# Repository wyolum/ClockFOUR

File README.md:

ClockFOUR
=========

ClockFOUR is a word clock that tells time with words.  It has a 14x13 matrix of letters that, when illuminated, tells time to the minute.  e.g. SEVENTEEN MINUTES PAST FOUR  The clock is 28 x 28 x ~2.6 cm.  The main PCB is approximately 24 x 22 cm and has 182 RGB WS2812B pixels on the front.  The back of the PCB contains an Arduino compatible 328P microprocessor and a DS3231 real time clock chip with 2032 battery backup.  Power is provided by a quality international multi-voltage 5V 3A power supply with barrel connector.

The user interface consists of two touch sensitive buttons wired to top two metal screw posts. Modes and settings are actuated by short taps and long presses.

Development team:
David Pincus (Project leader, software, hardware & design)
Josef Schneider (Software)
Anool Mahidharia (Hardware)

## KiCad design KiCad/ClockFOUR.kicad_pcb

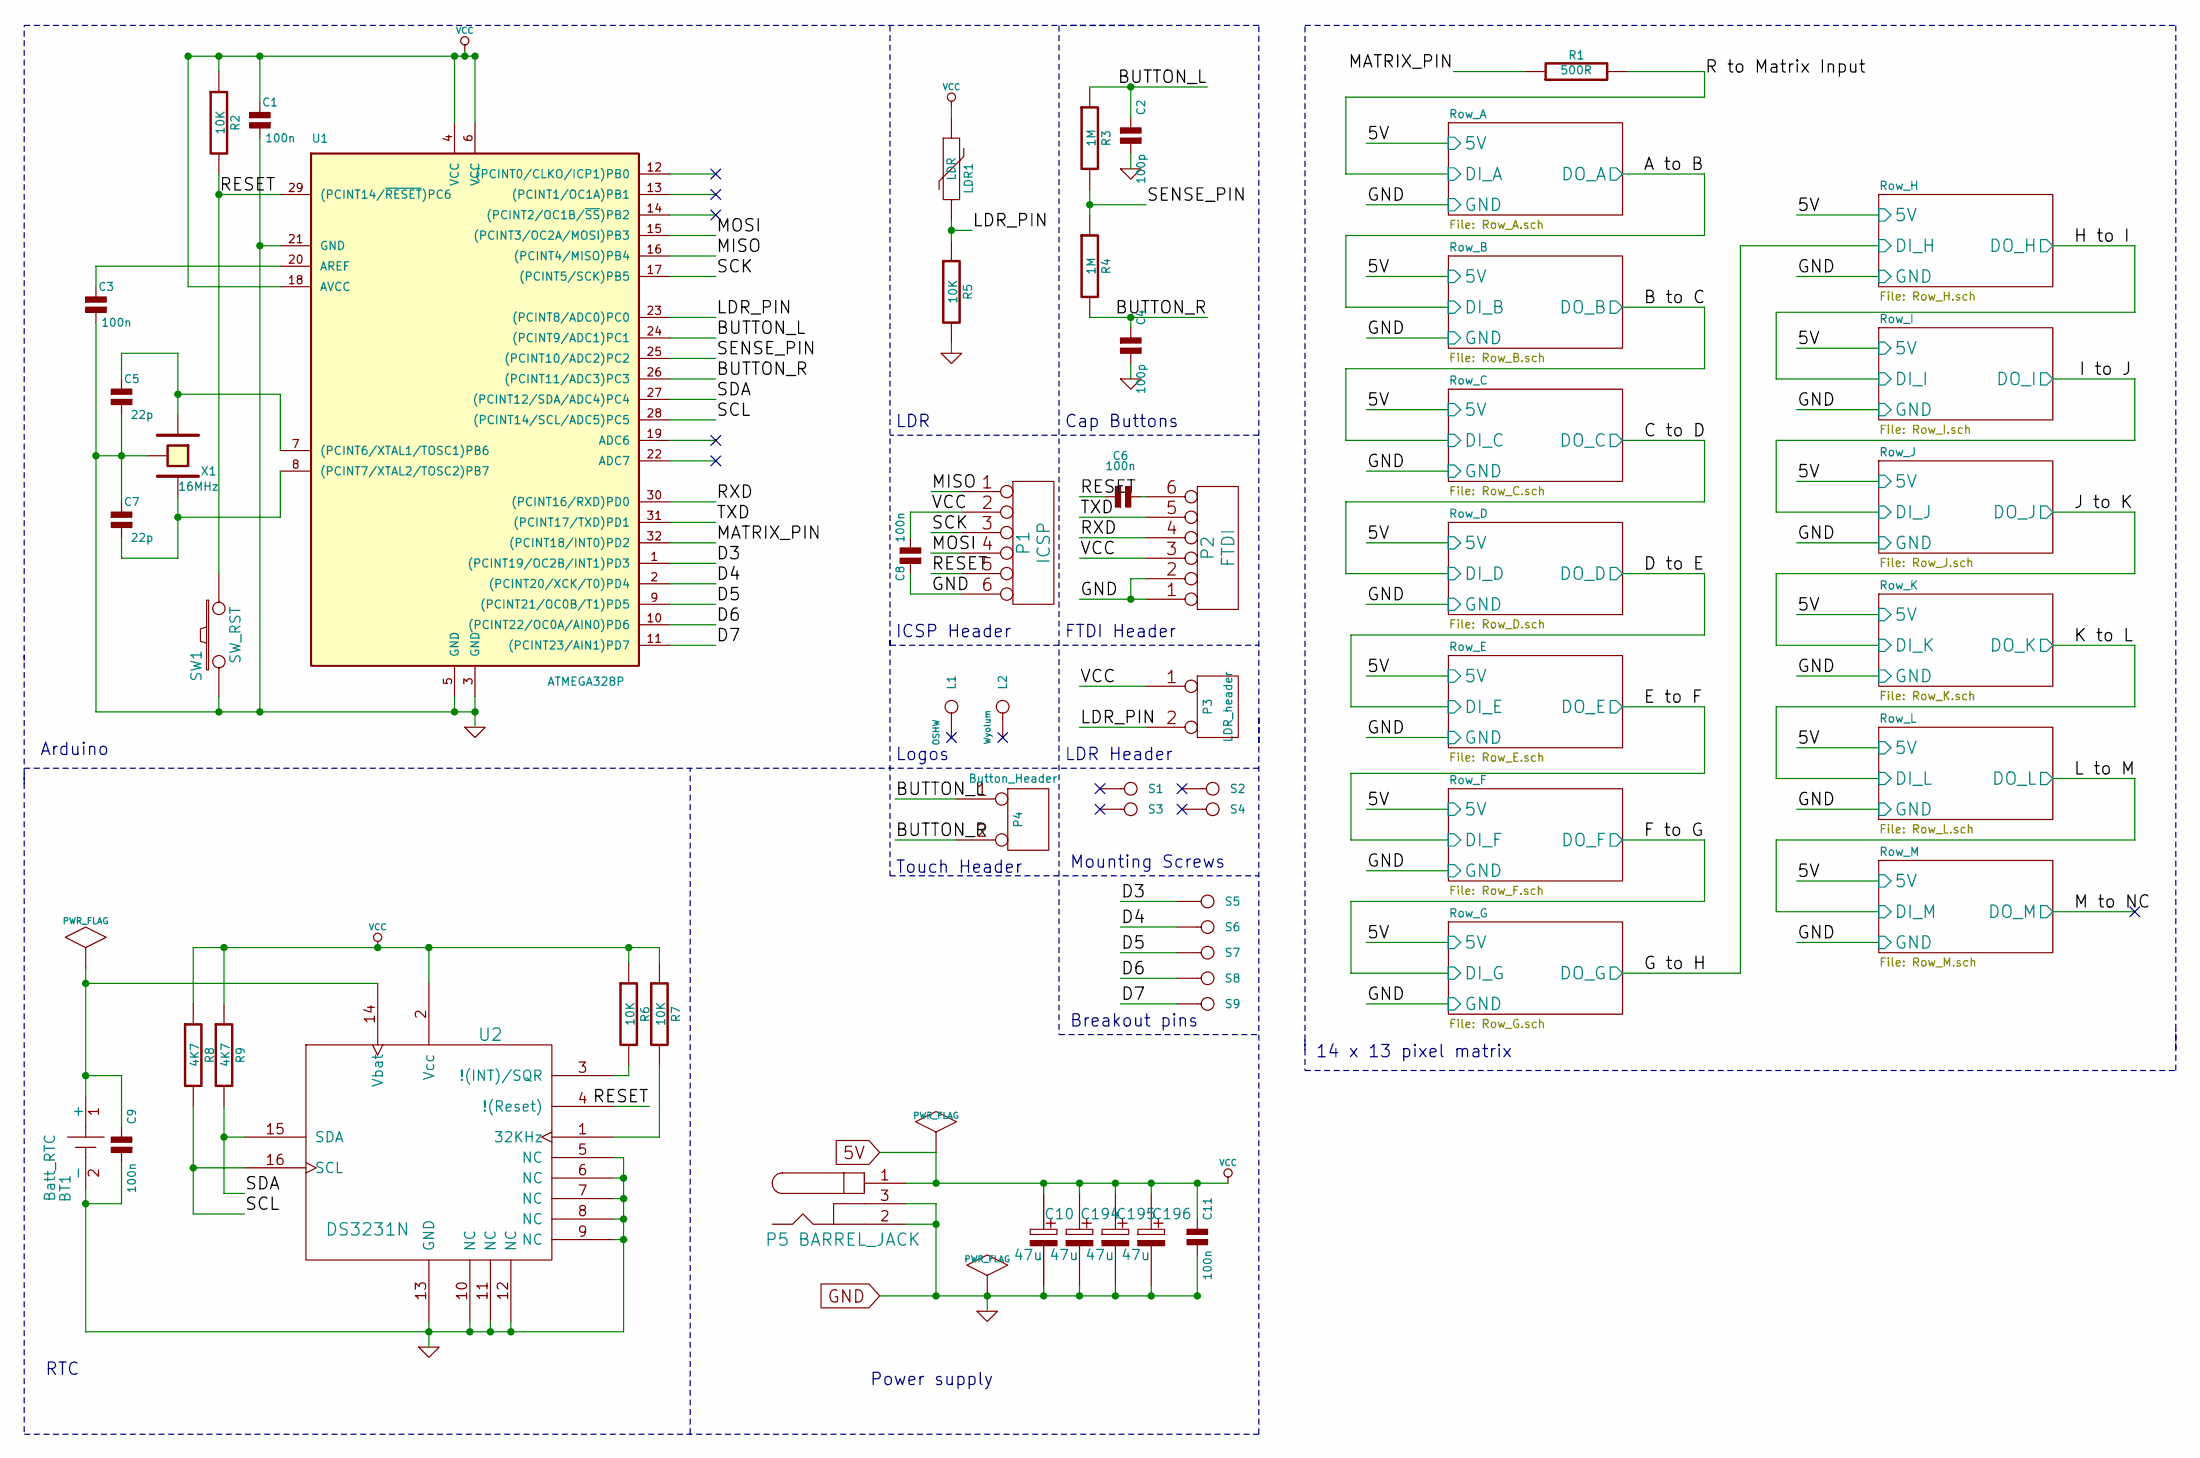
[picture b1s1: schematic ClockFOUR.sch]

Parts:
BT1: Batt_RTC; CR2032; Digikey BU2032SM-HD-GCT-ND
C1, C3, C6, C8, C9, C11: 100n; c_0805
C2, C4: 100p; c_0805
C5, C7: 22p; c_0805
C10, C194, C195, C196: 47u; c_2917
L1: OSHW; Logo_silk_OSHW_6x6mm
L2: Wyolum; Logo-WL3
LDR1: LDR; r_0805
P1: ICSP; ISP
P2: FTDI; Header_FTDI
P3: LDR_header; SIL-2
P4: Button_Header; SIL-2
P5: BARREL_JACK; JACK_PJ-047a
R1: 500R; r_0805
R2, R5, R6, R7: 10K; r_0805
R3, R4: 1M; r_0805
R8, R9: 4K7; r_0805
S1, S2, S3, S4: CONN_1; Screw_3mm
S5, S6, S7, S8, S9: CONN_1; BreakOutPad
SW1: SW_RST; SW_PB_V_H
U1: ATMEGA328P; TQFP32
U2: DS3231N; DS3231
X1: 16MHz

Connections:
5V: C1.1, C8.2, C10.1 (+), C11.1, C194.1 (+), C195.1 (+), C196.1 (+), LDR1.1, P1.2, P2.3, P3.1, P5.1, R2.1, R6.1, R7.1, R8.1, R9.1, U1.4 (VCC), U1.6 (VCC), U1.18 (AVCC), U2.2 (Vcc); also elsewhere on the board
/BUTTON_L: C2.1, P4.1, R3.1, U1.24 ((PCINT9/ADC1)PC1)
/BUTTON_R: C4.1, P4.2 (PM), R4.2, U1.26 ((PCINT11/ADC3)PC3)
/D3: S5.1, U1.1 ((PCINT19/OC2B/INT1)PD3)
/D4: S6.1, U1.2 ((PCINT20/XCK/T0)PD4)
/D5: S7.1, U1.9 ((PCINT21/OC0B/T1)PD5)
/D6: S8.1, U1.10 ((PCINT22/OC0A/AIN0)PD6)
/D7: S9.1, U1.11 ((PCINT23/AIN1)PD7)
/LDR_PIN: LDR1.2, P3.2 (PM), R5.1, U1.23 ((PCINT8/ADC0)PC0)
/MATRIX_PIN: R1.1, U1.32 ((PCINT18/INT0)PD2)
/MISO: P1.1, U1.16 ((PCINT4/MISO)PB4)
/MOSI: P1.4, U1.15 ((PCINT3/OC2A/MOSI)PB3)
/RESET: C6.1, P1.5, R2.2, SW1.1, U1.29 ((PCINT14/~RESET~)PC6), U2.4 (!(Reset))
/RXD: P2.4, U1.30 ((PCINT16/RXD)PD0)
/Row_A/DI_A: R1.2; also elsewhere on the board
/SCK: P1.3, U1.17 ((PCINT5/SCK)PB5)
/SCL: R8.2, U1.28 ((PCINT14/SCL/ADC5)PC5), U2.16 (SCL)
/SDA: R9.2, U1.27 ((PCINT12/SDA/ADC4)PC4), U2.15 (SDA)
/SENSE_PIN: R3.2, R4.1, U1.25 ((PCINT10/ADC2)PC2)
/TXD: P2.5, U1.31 ((PCINT17/TXD)PD1)
GND: BT1.2 (-), C1.2, C2.2, C3.2, C4.2, C5.2, C7.1, C8.1, C9.2, C10.2 (-), C11.2, C194.2 (-), C195.2 (-), C196.2 (-), P1.6, P2.1, P2.2, P5.2, P5.3, R5.2, SW1.2, U1.3 (GND), U1.5 (GND), U1.21 (GND), U2.5 (NC), U2.6 (NC), U2.7 (NC), U2.8 (NC), U2.9 (NC), U2.10 (NC), U2.11 (NC), U2.12 (NC), U2.13 (GND), X1.3; also elsewhere on the board
unnamed: BT1.1 (+), C9.1, U2.14 (Vbat)
unnamed: C3.1, U1.20 (AREF)
unnamed: C5.1, U1.7 ((PCINT6/XTAL1/TOSC1)PB6), X1.1
unnamed: C6.2, P2.6
unnamed: C7.2, U1.8 ((PCINT7/XTAL2/TOSC2)PB7), X1.2
unnamed: R6.2, U2.3 (!(INT)/SQR)
unnamed: R7.2, U2.1 (32KHz)

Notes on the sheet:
14 x 13 pixel matrix
RTC
Power supply
LDR
Cap Buttons
Arduino
ICSP Header
FTDI Header
LDR Header
Logos
Mounting Screws
Touch Header
Breakout pins

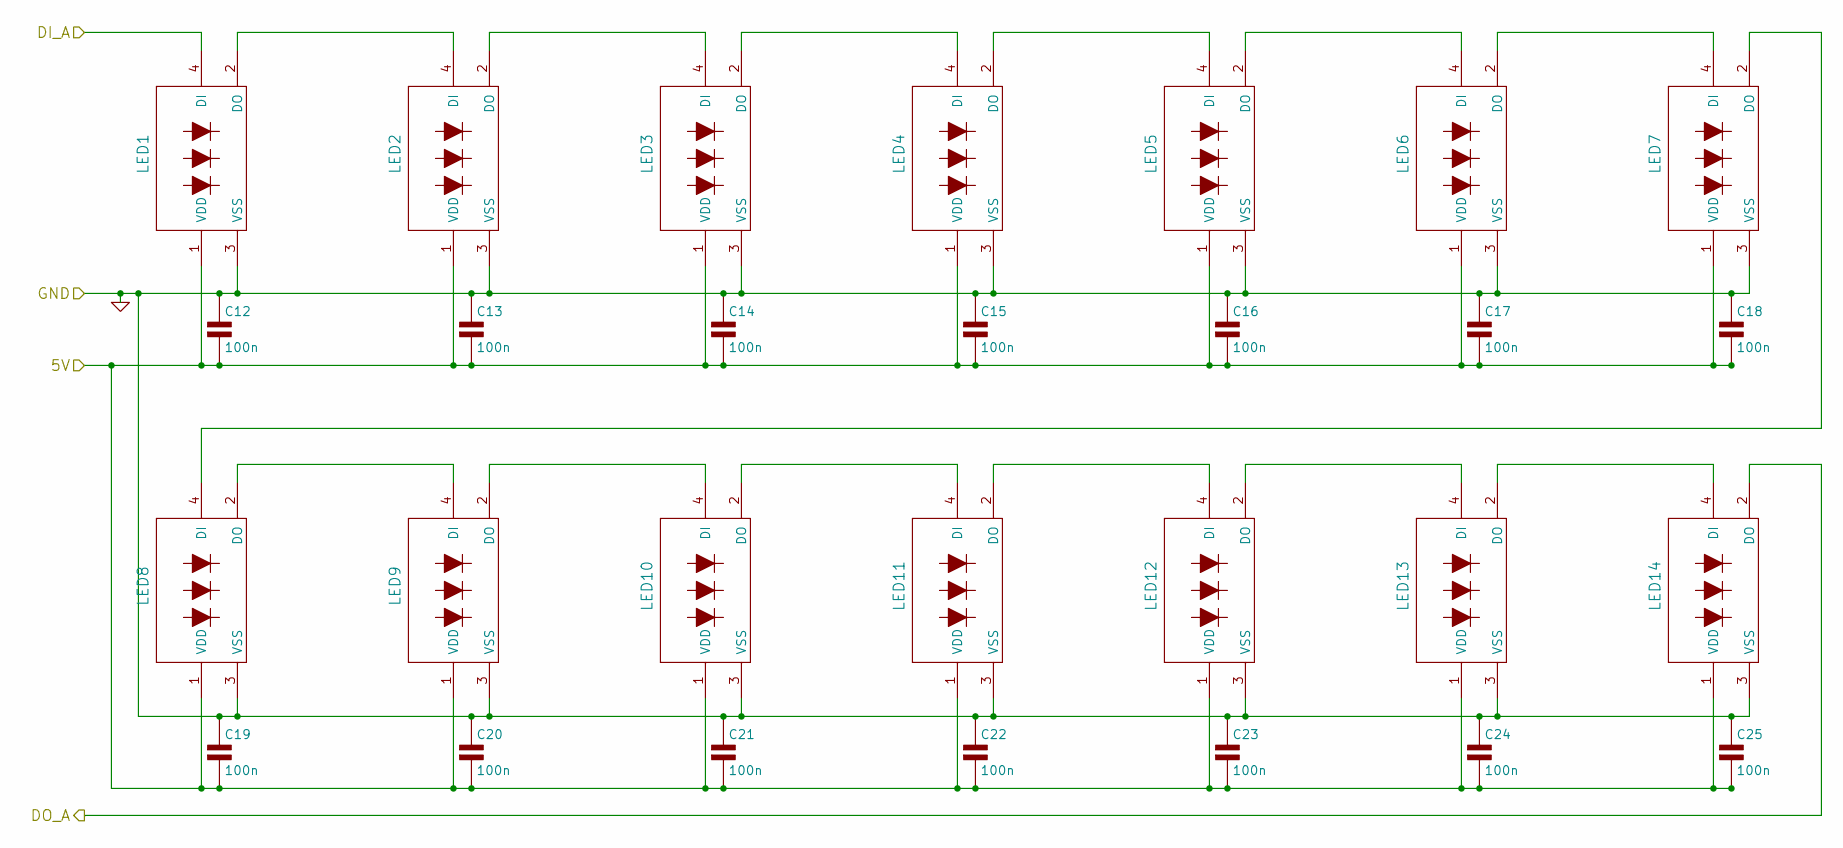
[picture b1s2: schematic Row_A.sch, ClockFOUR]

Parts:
C12, C13, C14, C15, C16, C17, C18, C19, C20, C21, C22, C23, C24, C25: 100n; c_0805
LED1, LED2, LED3, LED4, LED5, LED6, LED7, LED8, LED9, LED10, LED11, LED12, LED13, LED14: WS2812B

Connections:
5V: C12.2, C13.2, C14.2, C15.2, C16.2, C17.2, C18.2, C19.2, C20.2, C21.2, C22.2, C23.2, C24.2, C25.2, LED1.1 (VDD), LED2.1 (VDD), LED3.1 (VDD), LED4.1 (VDD), LED5.1 (VDD), LED6.1 (VDD), LED7.1 (VDD), LED8.1 (VDD), LED9.1 (VDD), LED10.1 (VDD), LED11.1 (VDD), LED12.1 (VDD), LED13.1 (VDD), LED14.1 (VDD); also elsewhere on the board
/Row_A/DI_A: LED1.4 (DI); also elsewhere on the board
/Row_B/DI_B: LED14.2 (DO); also elsewhere on the board
GND: C12.1, C13.1, C14.1, C15.1, C16.1, C17.1, C18.1, C19.1, C20.1, C21.1, C22.1, C23.1, C24.1, C25.1, LED1.3 (VSS), LED2.3 (VSS), LED3.3 (VSS), LED4.3 (VSS), LED5.3 (VSS), LED6.3 (VSS), LED7.3 (VSS), LED8.3 (VSS), LED9.3 (VSS), LED10.3 (VSS), LED11.3 (VSS), LED12.3 (VSS), LED13.3 (VSS), LED14.3 (VSS); also elsewhere on the board
unnamed: LED1.2 (DO), LED2.4 (DI)
unnamed: LED2.2 (DO), LED3.4 (DI)
unnamed: LED3.2 (DO), LED4.4 (DI)
unnamed: LED4.2 (DO), LED5.4 (DI)
unnamed: LED5.2 (DO), LED6.4 (DI)
unnamed: LED6.2 (DO), LED7.4 (DI)
unnamed: LED7.2 (DO), LED8.4 (DI)
unnamed: LED8.2 (DO), LED9.4 (DI)
unnamed: LED10.2 (DO), LED11.4 (DI)
unnamed: LED9.2 (DO), LED10.4 (DI)
unnamed: LED11.2 (DO), LED12.4 (DI)
unnamed: LED12.2 (DO), LED13.4 (DI)
unnamed: LED13.2 (DO), LED14.4 (DI)

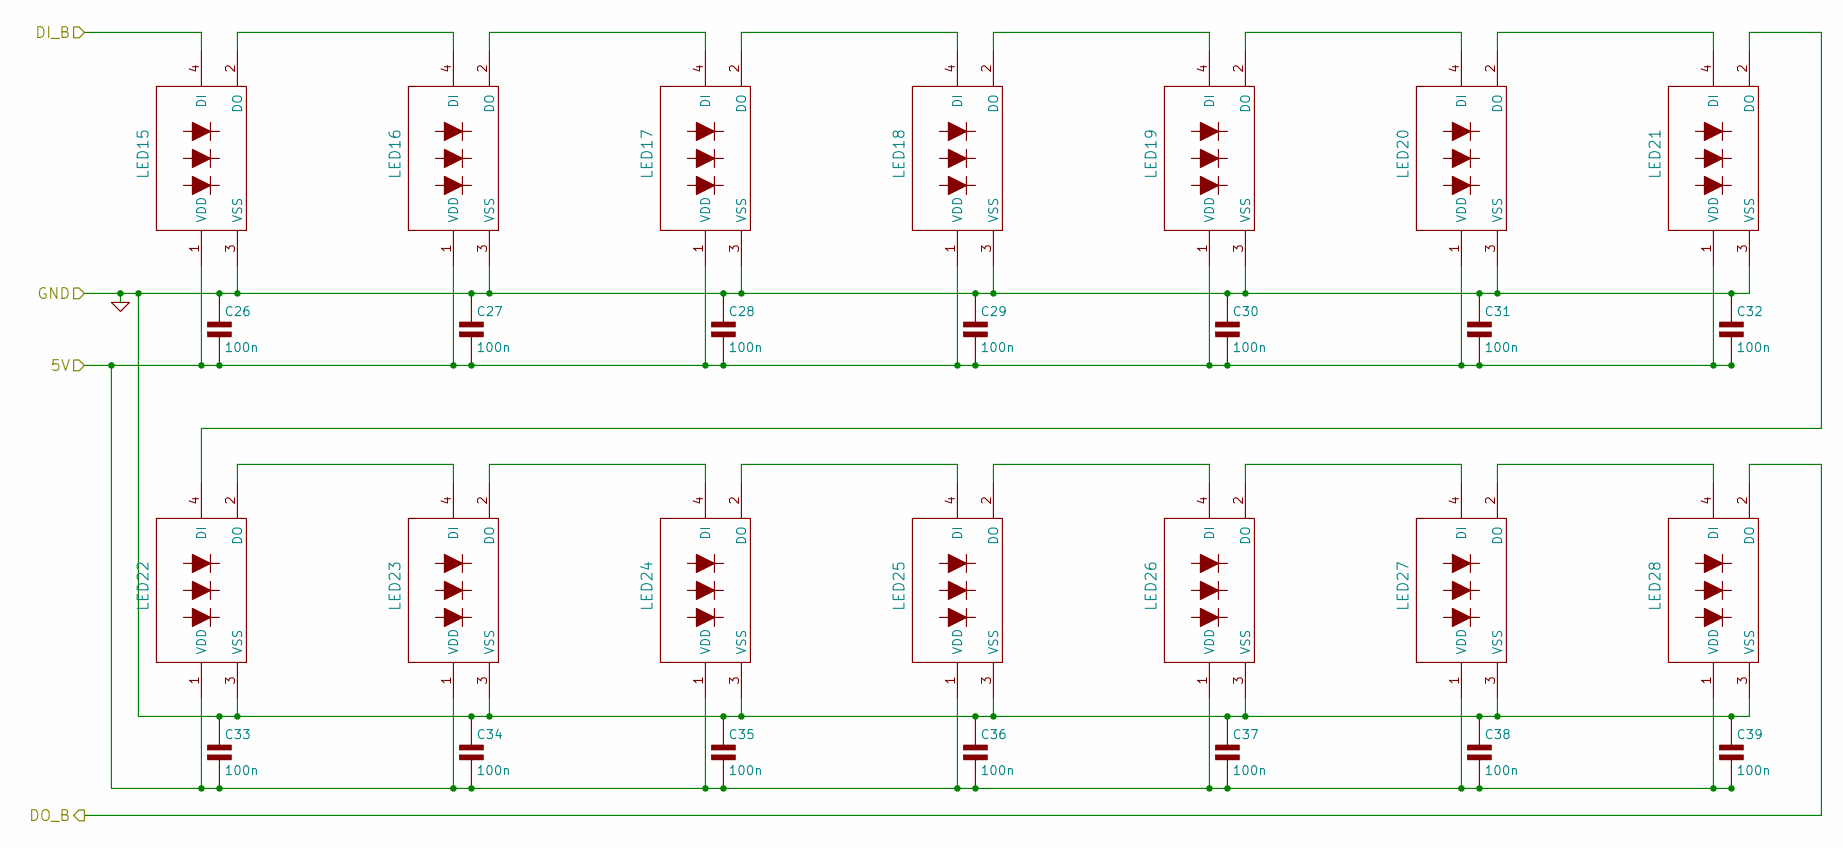
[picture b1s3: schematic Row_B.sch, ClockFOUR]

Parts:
C26, C27, C28, C29, C30, C31, C32, C33, C34, C35, C36, C37, C38, C39: 100n; c_0805
LED15, LED16, LED17, LED18, LED19, LED20, LED21, LED22, LED23, LED24, LED25, LED26, LED27, LED28: WS2812B

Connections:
5V: C26.2, C27.2, C28.2, C29.2, C30.2, C31.2, C32.2, C33.2, C34.2, C35.2, C36.2, C37.2, C38.2, C39.2, LED15.1 (VDD), LED16.1 (VDD), LED17.1 (VDD), LED18.1 (VDD), LED19.1 (VDD), LED20.1 (VDD), LED21.1 (VDD), LED22.1 (VDD), LED23.1 (VDD), LED24.1 (VDD), LED25.1 (VDD), LED26.1 (VDD), LED27.1 (VDD), LED28.1 (VDD); also elsewhere on the board
/Row_B/DI_B: LED15.4 (DI); also elsewhere on the board
/Row_C/DI_C: LED28.2 (DO); also elsewhere on the board
GND: C26.1, C27.1, C28.1, C29.1, C30.1, C31.1, C32.1, C33.1, C34.1, C35.1, C36.1, C37.1, C38.1, C39.1, LED15.3 (VSS), LED16.3 (VSS), LED17.3 (VSS), LED18.3 (VSS), LED19.3 (VSS), LED20.3 (VSS), LED21.3 (VSS), LED22.3 (VSS), LED23.3 (VSS), LED24.3 (VSS), LED25.3 (VSS), LED26.3 (VSS), LED27.3 (VSS), LED28.3 (VSS); also elsewhere on the board
unnamed: LED15.2 (DO), LED16.4 (DI)
unnamed: LED16.2 (DO), LED17.4 (DI)
unnamed: LED17.2 (DO), LED18.4 (DI)
unnamed: LED18.2 (DO), LED19.4 (DI)
unnamed: LED19.2 (DO), LED20.4 (DI)
unnamed: LED20.2 (DO), LED21.4 (DI)
unnamed: LED21.2 (DO), LED22.4 (DI)
unnamed: LED22.2 (DO), LED23.4 (DI)
unnamed: LED23.2 (DO), LED24.4 (DI)
unnamed: LED24.2 (DO), LED25.4 (DI)
unnamed: LED25.2 (DO), LED26.4 (DI)
unnamed: LED26.2 (DO), LED27.4 (DI)
unnamed: LED27.2 (DO), LED28.4 (DI)

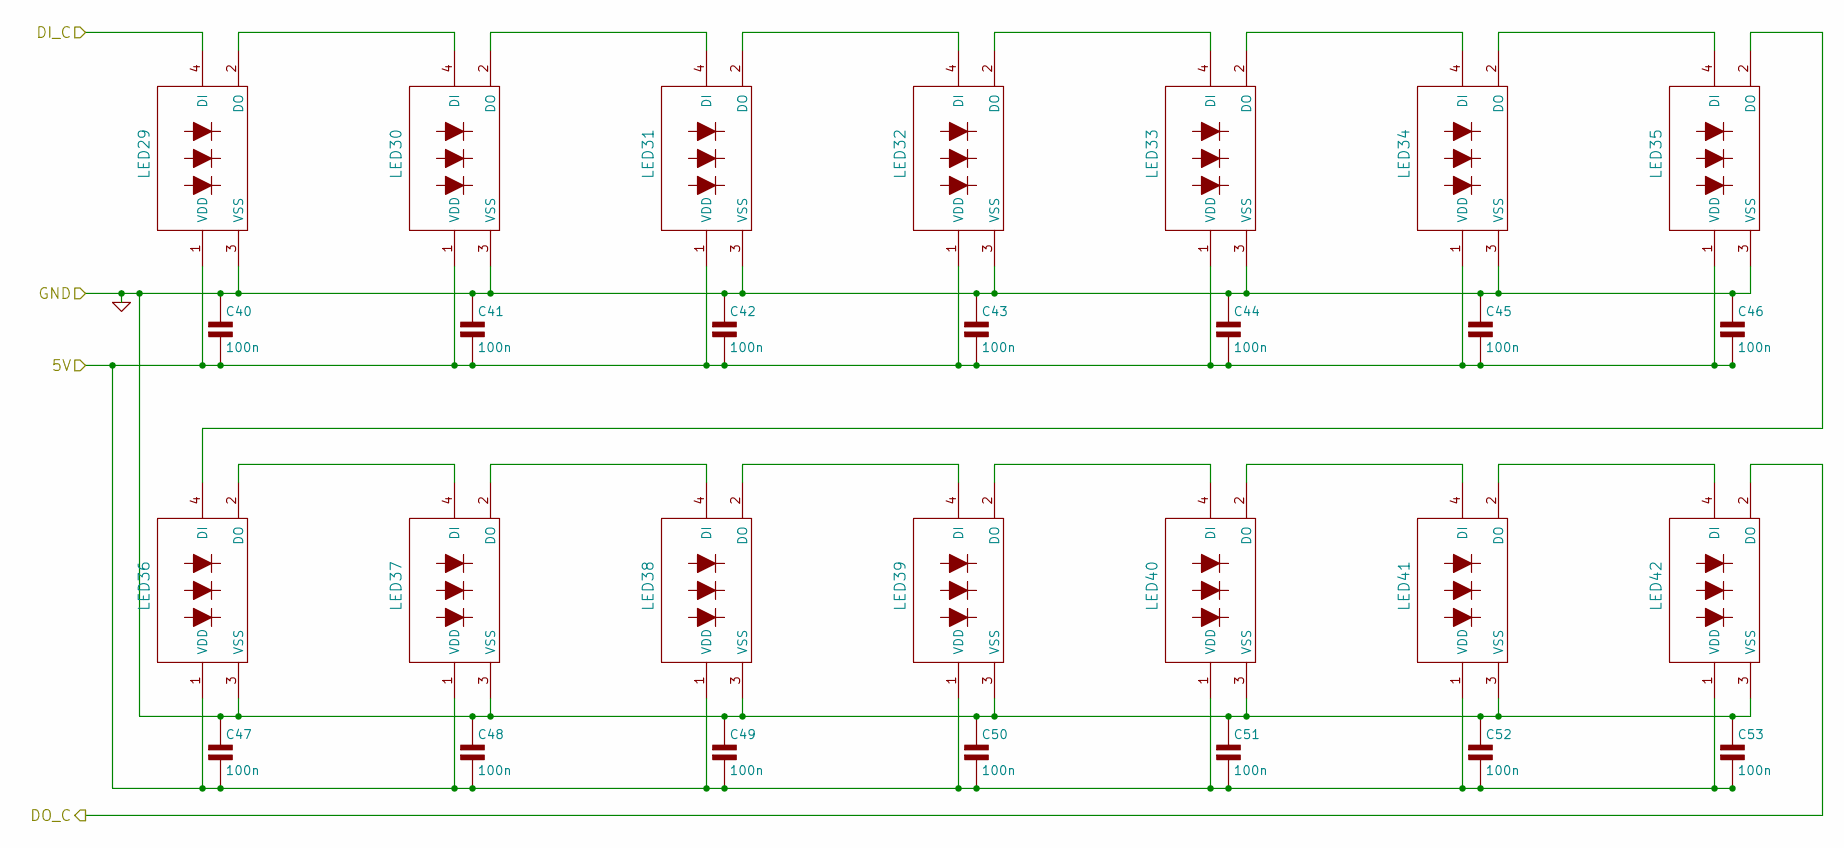
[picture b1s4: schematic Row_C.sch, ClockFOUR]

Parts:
C40, C41, C42, C43, C44, C45, C46, C47, C48, C49, C50, C51, C52, C53: 100n; c_0805
LED29, LED30, LED31, LED32, LED33, LED34, LED35, LED36, LED37, LED38, LED39, LED40, LED41, LED42: WS2812B; RGB_WS2811B

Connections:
5V: C40.2, C41.2, C42.2, C43.2, C44.2, C45.2, C46.2, C47.2, C48.2, C49.2, C50.2, C51.2, C52.2, C53.2, LED29.1 (VDD), LED30.1 (VDD), LED31.1 (VDD), LED32.1 (VDD), LED33.1 (VDD), LED34.1 (VDD), LED35.1 (VDD), LED36.1 (VDD), LED37.1 (VDD), LED38.1 (VDD), LED39.1 (VDD), LED40.1 (VDD), LED41.1 (VDD), LED42.1 (VDD); also elsewhere on the board
/Row_C/DI_C: LED29.4 (DI); also elsewhere on the board
/Row_D/DI_D: LED42.2 (DO); also elsewhere on the board
GND: C40.1, C41.1, C42.1, C43.1, C44.1, C45.1, C46.1, C47.1, C48.1, C49.1, C50.1, C51.1, C52.1, C53.1, LED29.3 (VSS), LED30.3 (VSS), LED31.3 (VSS), LED32.3 (VSS), LED33.3 (VSS), LED34.3 (VSS), LED35.3 (VSS), LED36.3 (VSS), LED37.3 (VSS), LED38.3 (VSS), LED39.3 (VSS), LED40.3 (VSS), LED41.3 (VSS), LED42.3 (VSS); also elsewhere on the board
unnamed: LED29.2 (DO), LED30.4 (DI)
unnamed: LED30.2 (DO), LED31.4 (DI)
unnamed: LED31.2 (DO), LED32.4 (DI)
unnamed: LED32.2 (DO), LED33.4 (DI)
unnamed: LED33.2 (DO), LED34.4 (DI)
unnamed: LED34.2 (DO), LED35.4 (DI)
unnamed: LED35.2 (DO), LED36.4 (DI)
unnamed: LED36.2 (DO), LED37.4 (DI)
unnamed: LED37.2 (DO), LED38.4 (DI)
unnamed: LED38.2 (DO), LED39.4 (DI)
unnamed: LED39.2 (DO), LED40.4 (DI)
unnamed: LED40.2 (DO), LED41.4 (DI)
unnamed: LED41.2 (DO), LED42.4 (DI)

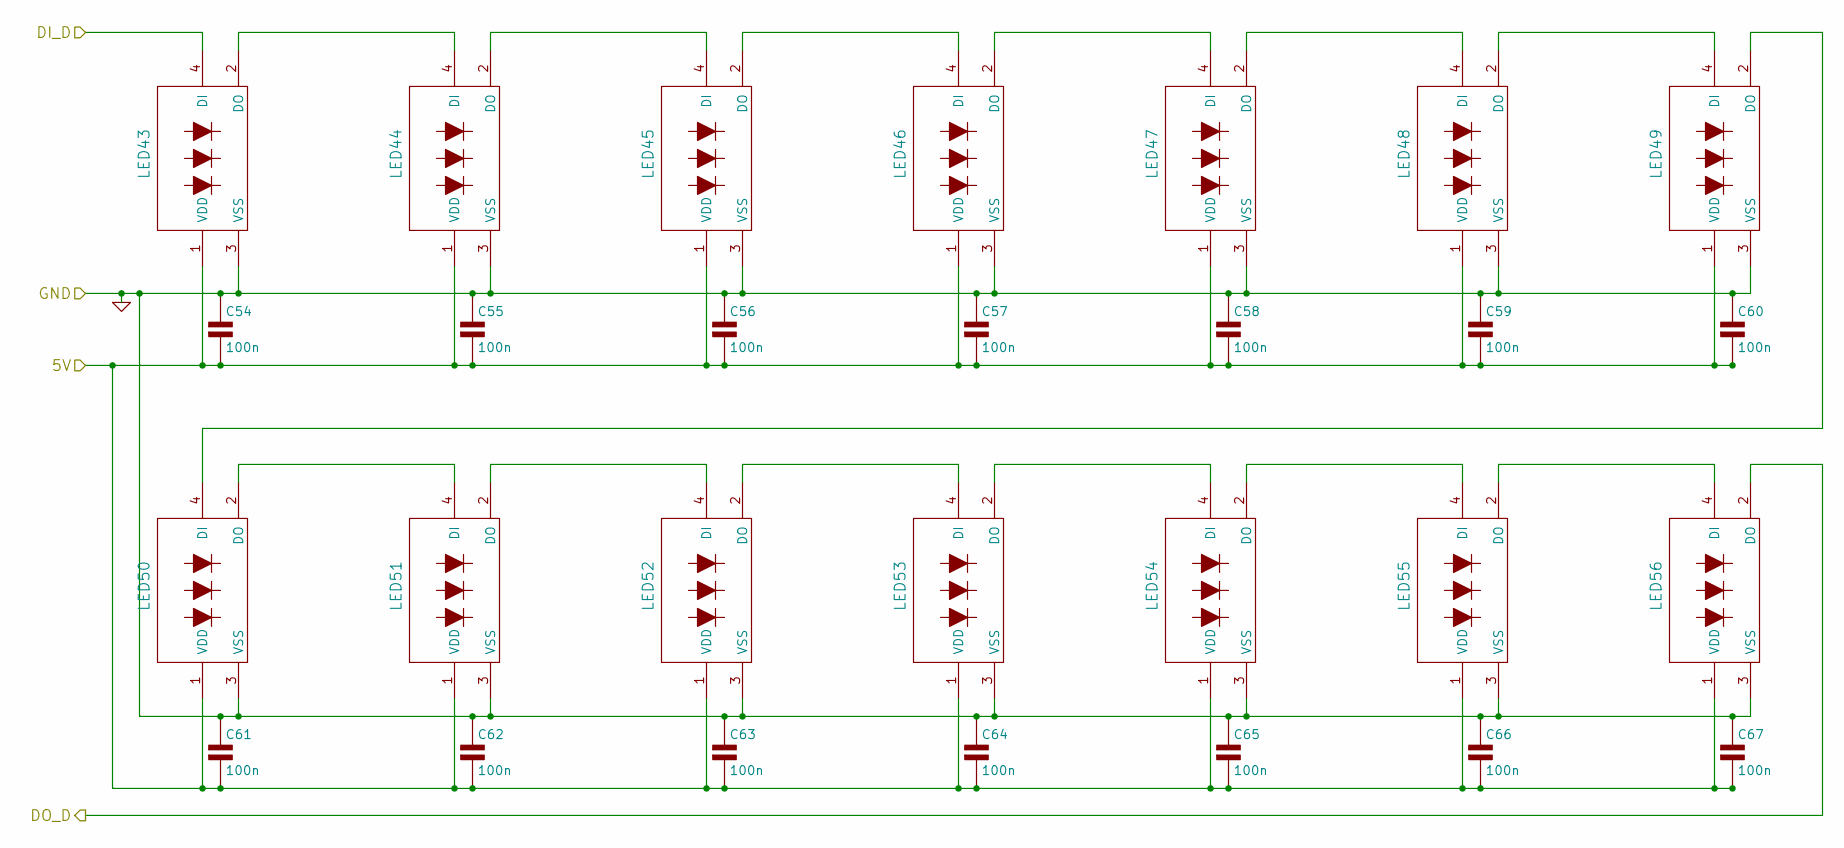
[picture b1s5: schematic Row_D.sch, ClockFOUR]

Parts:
C54, C55, C56, C57, C58, C59, C60, C61, C62, C63, C64, C65, C66, C67: 100n; c_0805
LED43, LED44, LED45, LED46, LED47, LED48, LED49, LED50, LED51, LED52, LED53, LED54, LED55, LED56: WS2812B; RGB_WS2811B

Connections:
5V: C54.2, C55.2, C56.2, C57.2, C58.2, C59.2, C60.2, C61.2, C62.2, C63.2, C64.2, C65.2, C66.2, C67.2, LED43.1 (VDD), LED44.1 (VDD), LED45.1 (VDD), LED46.1 (VDD), LED47.1 (VDD), LED48.1 (VDD), LED49.1 (VDD), LED50.1 (VDD), LED51.1 (VDD), LED52.1 (VDD), LED53.1 (VDD), LED54.1 (VDD), LED55.1 (VDD), LED56.1 (VDD); also elsewhere on the board
/Row_D/DI_D: LED43.4 (DI); also elsewhere on the board
/Row_E/DI_E: LED56.2 (DO); also elsewhere on the board
GND: C54.1, C55.1, C56.1, C57.1, C58.1, C59.1, C60.1, C61.1, C62.1, C63.1, C64.1, C65.1, C66.1, C67.1, LED43.3 (VSS), LED44.3 (VSS), LED45.3 (VSS), LED46.3 (VSS), LED47.3 (VSS), LED48.3 (VSS), LED49.3 (VSS), LED50.3 (VSS), LED51.3 (VSS), LED52.3 (VSS), LED53.3 (VSS), LED54.3 (VSS), LED55.3 (VSS), LED56.3 (VSS); also elsewhere on the board
unnamed: LED43.2 (DO), LED44.4 (DI)
unnamed: LED44.2 (DO), LED45.4 (DI)
unnamed: LED45.2 (DO), LED46.4 (DI)
unnamed: LED46.2 (DO), LED47.4 (DI)
unnamed: LED47.2 (DO), LED48.4 (DI)
unnamed: LED48.2 (DO), LED49.4 (DI)
unnamed: LED49.2 (DO), LED50.4 (DI)
unnamed: LED50.2 (DO), LED51.4 (DI)
unnamed: LED51.2 (DO), LED52.4 (DI)
unnamed: LED52.2 (DO), LED53.4 (DI)
unnamed: LED53.2 (DO), LED54.4 (DI)
unnamed: LED54.2 (DO), LED55.4 (DI)
unnamed: LED55.2 (DO), LED56.4 (DI)

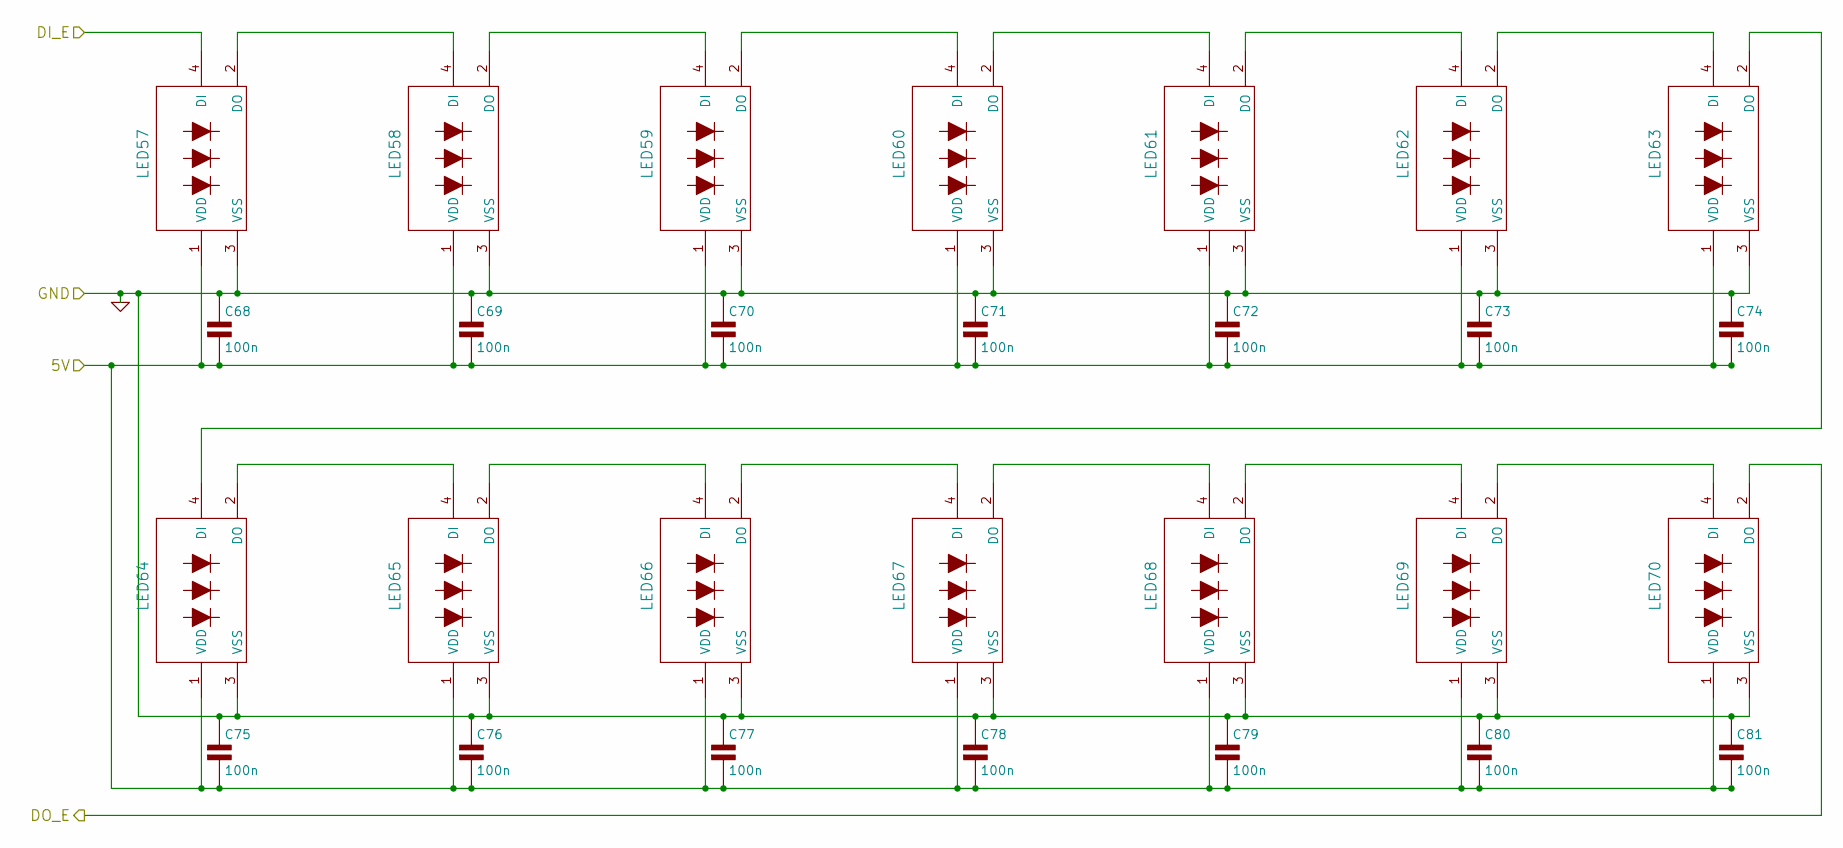
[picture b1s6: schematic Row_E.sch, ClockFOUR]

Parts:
C68, C69, C70, C71, C72, C73, C74, C75, C76, C77, C78, C79, C80, C81: 100n; c_0805
LED57, LED58, LED59, LED60, LED61, LED62, LED63, LED64, LED65, LED66, LED67, LED68, LED69, LED70: WS2812B

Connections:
5V: C68.2, C69.2, C70.2, C71.2, C72.2, C73.2, C74.2, C75.2, C76.2, C77.2, C78.2, C79.2, C80.2, C81.2, LED57.1 (VDD), LED58.1 (VDD), LED59.1 (VDD), LED60.1 (VDD), LED61.1 (VDD), LED62.1 (VDD), LED63.1 (VDD), LED64.1 (VDD), LED65.1 (VDD), LED66.1 (VDD), LED67.1 (VDD), LED68.1 (VDD), LED69.1 (VDD), LED70.1 (VDD); also elsewhere on the board
/Row_E/DI_E: LED57.4 (DI); also elsewhere on the board
/Row_F/DI_F: LED70.2 (DO); also elsewhere on the board
GND: C68.1, C69.1, C70.1, C71.1, C72.1, C73.1, C74.1, C75.1, C76.1, C77.1, C78.1, C79.1, C80.1, C81.1, LED57.3 (VSS), LED58.3 (VSS), LED59.3 (VSS), LED60.3 (VSS), LED61.3 (VSS), LED62.3 (VSS), LED63.3 (VSS), LED64.3 (VSS), LED65.3 (VSS), LED66.3 (VSS), LED67.3 (VSS), LED68.3 (VSS), LED69.3 (VSS), LED70.3 (VSS); also elsewhere on the board
unnamed: LED57.2 (DO), LED58.4 (DI)
unnamed: LED58.2 (DO), LED59.4 (DI)
unnamed: LED59.2 (DO), LED60.4 (DI)
unnamed: LED60.2 (DO), LED61.4 (DI)
unnamed: LED61.2 (DO), LED62.4 (DI)
unnamed: LED62.2 (DO), LED63.4 (DI)
unnamed: LED63.2 (DO), LED64.4 (DI)
unnamed: LED64.2 (DO), LED65.4 (DI)
unnamed: LED65.2 (DO), LED66.4 (DI)
unnamed: LED66.2 (DO), LED67.4 (DI)
unnamed: LED67.2 (DO), LED68.4 (DI)
unnamed: LED68.2 (DO), LED69.4 (DI)
unnamed: LED69.2 (DO), LED70.4 (DI)

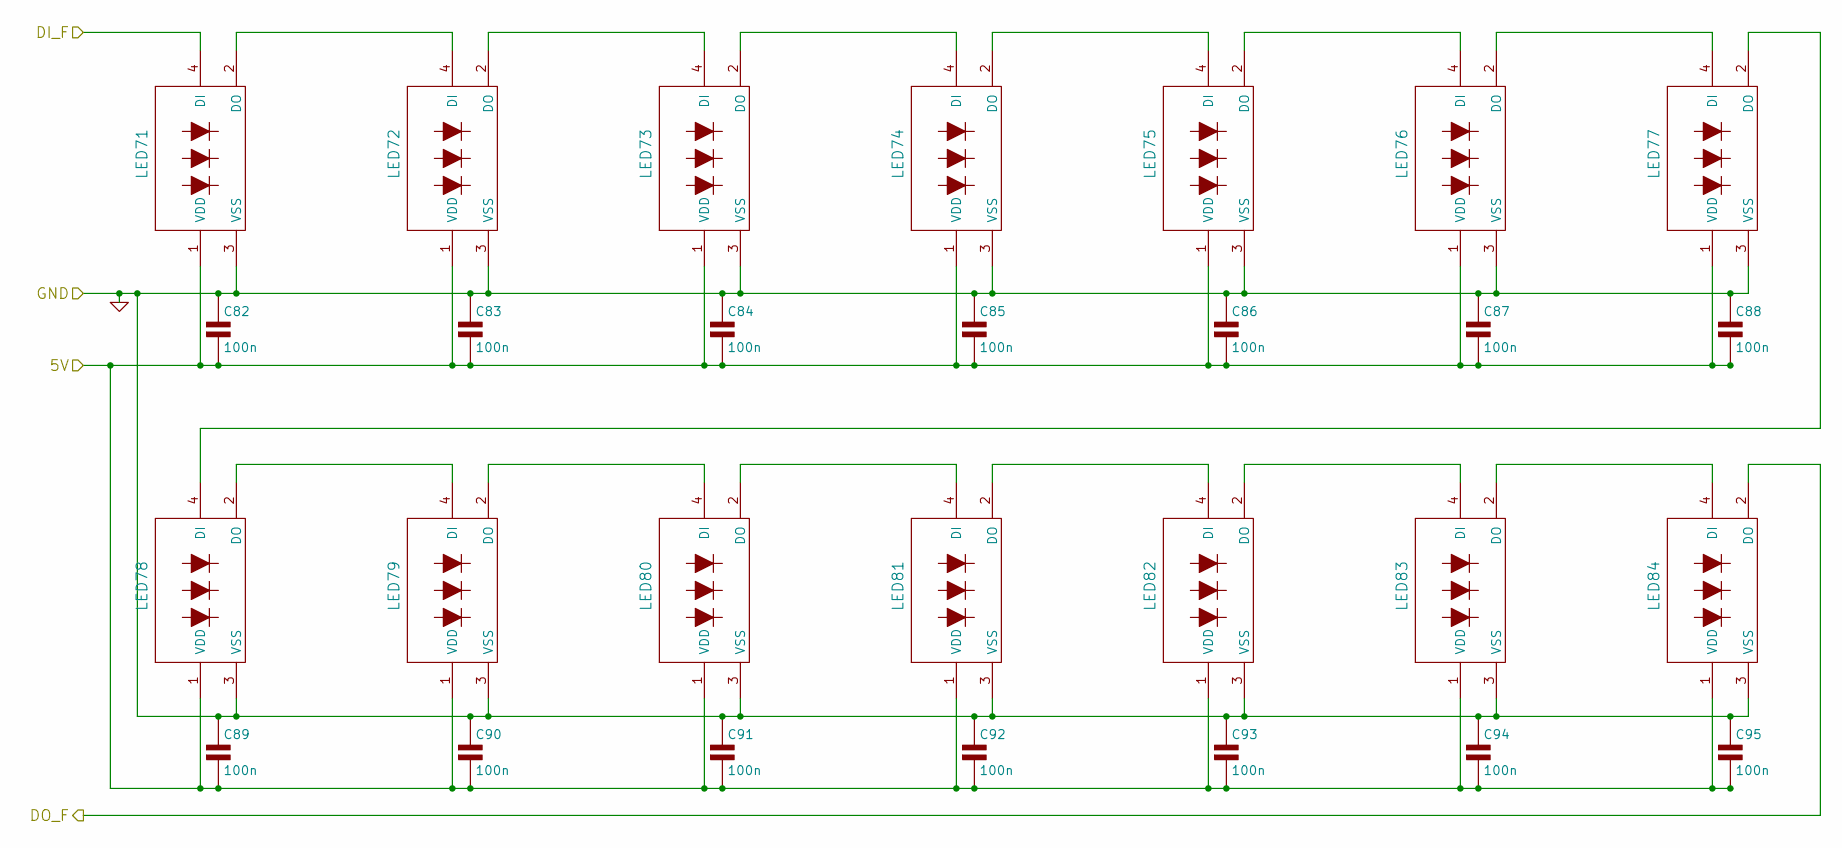
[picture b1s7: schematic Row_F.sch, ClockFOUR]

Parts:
C82, C83, C84, C85, C86, C87, C88, C89, C90, C91, C92, C93, C94, C95: 100n; c_0805
LED71, LED72, LED73, LED74, LED75, LED76, LED77, LED78, LED79, LED80, LED81, LED82, LED83, LED84: WS2812B

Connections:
5V: C82.2, C83.2, C84.2, C85.2, C86.2, C87.2, C88.2, C89.2, C90.2, C91.2, C92.2, C93.2, C94.2, C95.2, LED71.1 (VDD), LED72.1 (VDD), LED73.1 (VDD), LED74.1 (VDD), LED75.1 (VDD), LED76.1 (VDD), LED77.1 (VDD), LED78.1 (VDD), LED79.1 (VDD), LED80.1 (VDD), LED81.1 (VDD), LED82.1 (VDD), LED83.1 (VDD), LED84.1 (VDD); also elsewhere on the board
/Row_F/DI_F: LED71.4 (DI); also elsewhere on the board
/Row_G/DI_G: LED84.2 (DO); also elsewhere on the board
GND: C82.1, C83.1, C84.1, C85.1, C86.1, C87.1, C88.1, C89.1, C90.1, C91.1, C92.1, C93.1, C94.1, C95.1, LED71.3 (VSS), LED72.3 (VSS), LED73.3 (VSS), LED74.3 (VSS), LED75.3 (VSS), LED76.3 (VSS), LED77.3 (VSS), LED78.3 (VSS), LED79.3 (VSS), LED80.3 (VSS), LED81.3 (VSS), LED82.3 (VSS), LED83.3 (VSS), LED84.3 (VSS); also elsewhere on the board
unnamed: LED71.2 (DO), LED72.4 (DI)
unnamed: LED72.2 (DO), LED73.4 (DI)
unnamed: LED73.2 (DO), LED74.4 (DI)
unnamed: LED74.2 (DO), LED75.4 (DI)
unnamed: LED75.2 (DO), LED76.4 (DI)
unnamed: LED76.2 (DO), LED77.4 (DI)
unnamed: LED77.2 (DO), LED78.4 (DI)
unnamed: LED78.2 (DO), LED79.4 (DI)
unnamed: LED79.2 (DO), LED80.4 (DI)
unnamed: LED80.2 (DO), LED81.4 (DI)
unnamed: LED81.2 (DO), LED82.4 (DI)
unnamed: LED82.2 (DO), LED83.4 (DI)
unnamed: LED83.2 (DO), LED84.4 (DI)

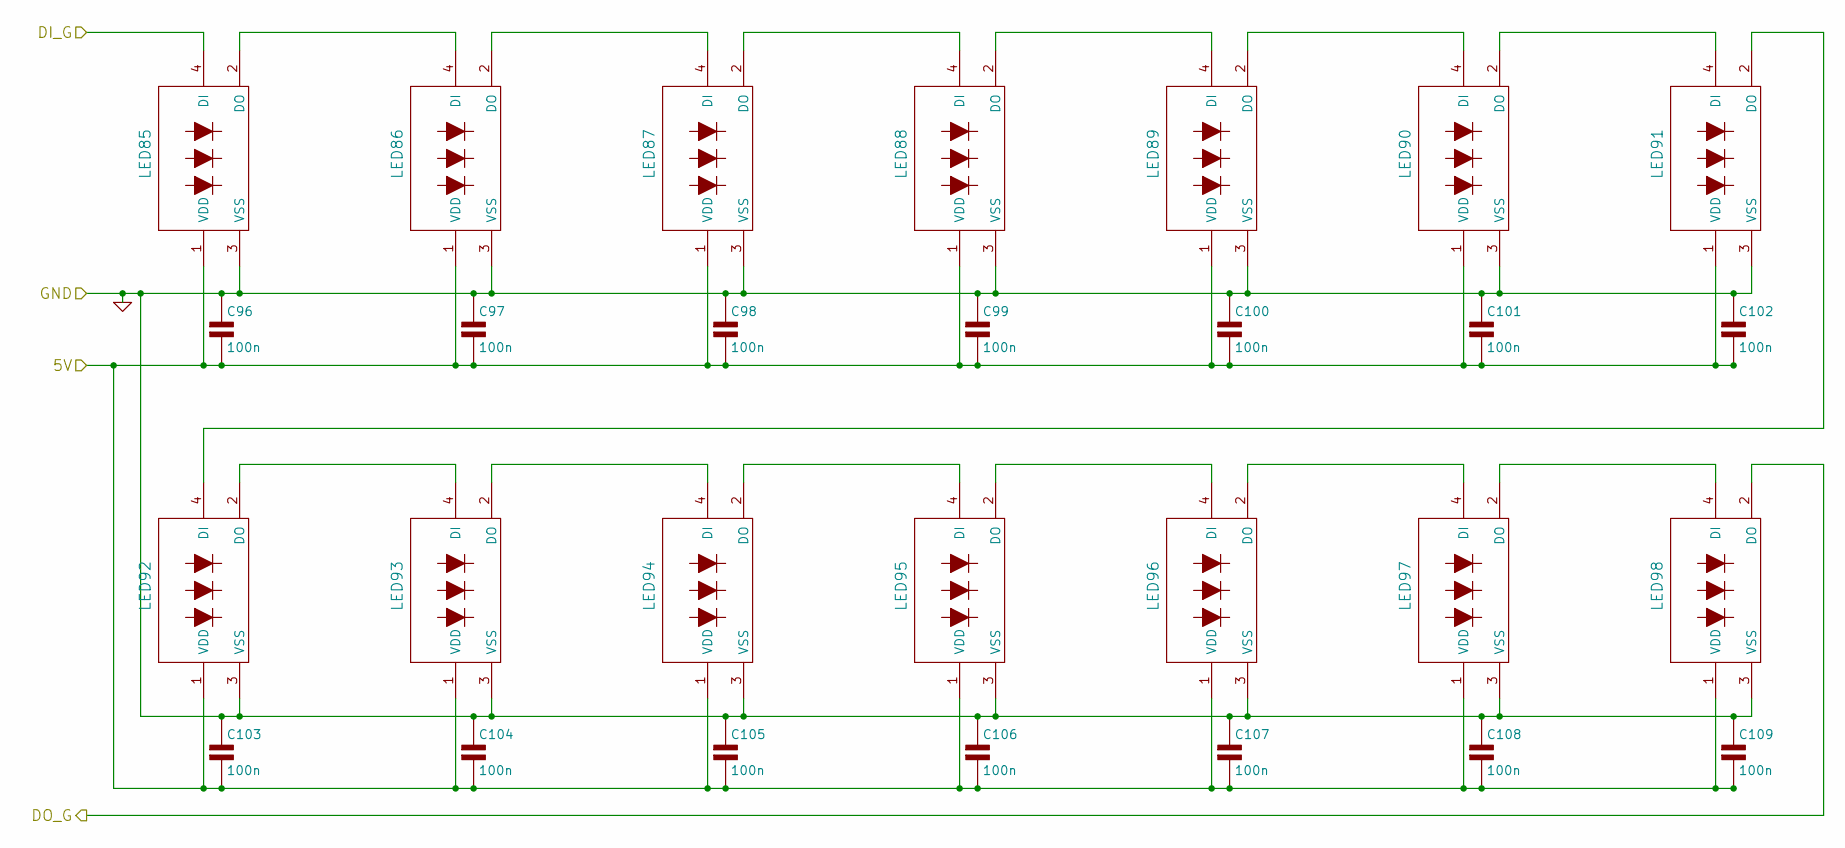
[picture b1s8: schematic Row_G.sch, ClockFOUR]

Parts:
C96, C97, C98, C99, C100, C101, C102, C103, C104, C105, C106, C107, C108, C109: 100n; c_0805
LED85, LED86, LED87, LED88, LED89, LED90, LED91, LED92, LED93, LED94, LED95, LED96, LED97, LED98: WS2812B

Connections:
5V: C96.2, C97.2, C98.2, C99.2, C100.2, C101.2, C102.2, C103.2, C104.2, C105.2, C106.2, C107.2, C108.2, C109.2, LED85.1 (VDD), LED86.1 (VDD), LED87.1 (VDD), LED88.1 (VDD), LED89.1 (VDD), LED90.1 (VDD), LED91.1 (VDD), LED92.1 (VDD), LED93.1 (VDD), LED94.1 (VDD), LED95.1 (VDD), LED96.1 (VDD), LED97.1 (VDD), LED98.1 (VDD); also elsewhere on the board
/Row_G/DI_G: LED85.4 (DI); also elsewhere on the board
/Row_H/DI_H: LED98.2 (DO); also elsewhere on the board
GND: C96.1, C97.1, C98.1, C99.1, C100.1, C101.1, C102.1, C103.1, C104.1, C105.1, C106.1, C107.1, C108.1, C109.1, LED85.3 (VSS), LED86.3 (VSS), LED87.3 (VSS), LED88.3 (VSS), LED89.3 (VSS), LED90.3 (VSS), LED91.3 (VSS), LED92.3 (VSS), LED93.3 (VSS), LED94.3 (VSS), LED95.3 (VSS), LED96.3 (VSS), LED97.3 (VSS), LED98.3 (VSS); also elsewhere on the board
unnamed: LED85.2 (DO), LED86.4 (DI)
unnamed: LED86.2 (DO), LED87.4 (DI)
unnamed: LED87.2 (DO), LED88.4 (DI)
unnamed: LED88.2 (DO), LED89.4 (DI)
unnamed: LED89.2 (DO), LED90.4 (DI)
unnamed: LED90.2 (DO), LED91.4 (DI)
unnamed: LED91.2 (DO), LED92.4 (DI)
unnamed: LED92.2 (DO), LED93.4 (DI)
unnamed: LED93.2 (DO), LED94.4 (DI)
unnamed: LED94.2 (DO), LED95.4 (DI)
unnamed: LED95.2 (DO), LED96.4 (DI)
unnamed: LED96.2 (DO), LED97.4 (DI)
unnamed: LED97.2 (DO), LED98.4 (DI)
